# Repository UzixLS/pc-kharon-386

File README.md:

## Kharon-386
10x10cm IBM PC compatible machine with 386 CPU, integrated VGA and sound.

More random photos: [link](https://cloud.err200.net/index.php/s/73TR85tYZkMm8Ax?path=%2Fkharon-386)

### Tech specs
* M6117D System-On-Chip with integrated 386SX40 (almost compatible) CPU and M1217B chipset
* 4MB RAM
* TVGA9000i VGA video
* ES1868F SoundBlasterPro-compatible sound
* SAM2695 MIDI synthesizer
* ESP8266 WiFi module
* PS/2 keyboard and mouse inputs
* 2xCOM ports
* CF card slot
* Real-time clock (RTC) with backup battery
* Integrated PC-speaker
* 5.1V microUSB power
* Two 4-layer 10x10cm PCBs + front/back panel PCB
* G738 or G706 enclosure

### Navigation
[release/pcb_main.rev.A1.pdf](release/pcb_main.rev.A1.pdf) - motherboard schematic and bill of materials  
[release/pcb_top.rev.A1.pdf](release/pcb_top.rev.A1.pdf) - video&sound board schematic and bill of materials  
[release/bom_interactive_main.rev.A1.html](https://htmlpreview.github.io/?https://github.com/UzixLS/pc-kharon-386/blob/master/release/bom_interactive_main.rev.A1.html) - motherboard interactive BOM  
[release/bom_interactive_top.rev.A1.html](https://htmlpreview.github.io/?https://github.com/UzixLS/pc-kharon-386/blob/master/release/bom_interactive_top.rev.A1.html) - video&sound board interactive BOM  
[release/gerber_main.rev.A1.zip](release/gerber_main.rev.A1.zip) - motherboard fabrication files  
[release/gerber_top.rev.A1.zip](release/gerber_top.rev.A1.zip) - video&sound board fabrication files  
[release/gerber_covers.rev.A.zip](release/gerber_covers.rev.A.zip) - front and back panel fabrication files  
[roms/M6117 - award+ami.bin](roms/M6117%20-%20award+ami.bin) - main BIOS image  
[roms/tvga9000i - D3.51 + D4.01E.bin](roms/tvga9000i%20-%20D3.51%20%2B%20D4.01E.bin) - VGA BIOS image  
[software/msdos622_compactflash_2GB.7z](software/msdos622_compactflash_2GB.7z) - CF card image with preinstalled MS-DOS 6.22 and all necessary drivers

### WiFi module
There is two options how to use WiFi module:
1. Zimodem ([link](https://github.com/bozimmerman/Zimodem)) - provides ability to connect to BBS via any terminal without using additional software. WiFi module is connected to COM4, so you can use any terminal to communicate with it using AT commands.
2. esp_slip_router ([link](https://github.com/martin-ger/esp_slip_router)) - provides ability to connect your machine to IP network just like as Ethernet. You need ETHERSLIP or similar packet driver for DOS.

To upload firmware you need USB-UART adapter with 3.3V signal levels. Connect GND, RX and TX lines to esp header located on main PCB at left, install BOOT/GND jumper and follow any ESP8266 firmware update guide that is available on the internet.

### Sound mixer
MIDI synthesizer is connected to the AUXB sound input of ES1868F. Usually this input named as "CD input" in mixer software.  
PC speaker is connected to the AUXA input.  
To obtain a minimum noise level, it is recommended to disable line input in the mixer.

### Changelog & current status
Main PCB:
* Rev.A - first release. Please note the [errata](pcb_main/rev.A/ERRATA.txt);
* Rev.A1 - fixed all rev.A issues; added switch for BIOS variant select; added optional -5V source. Please note the [errata](pcb_main/rev.A1/ERRATA.txt).

Top PCB:
* Rev.A - first release. Please note the [errata](pcb_top/rev.A/ERRATA.txt);
* Rev.A1 - fixed all rev.A issues; added switch for VGA BIOS variant select; removed VGA-disable switch; added EEPROM for ES1868.

Covers PCB:
* Rev.A - first release.

### Related projects
I want to express my appreciation to the authors of the following projects, which served as inspiration and as reference for my development:

[http://www.alexandrugroza.ro/microelectronics/system-design/isa-80386dx-sbmc/index.html](http://www.alexandrugroza.ro/microelectronics/system-design/isa-80386dx-sbmc/index.html) - 80386DX ISA single board microcomputer by Alexandru Groza  
[https://bitbucket.org/Haper/poisk-2-mainboard/src/master/](https://bitbucket.org/Haper/poisk-2-mainboard/src/master/) - XT compatible 8086-based machine, reverse engineered by Andrew Khapoknysh ([details](https://habr.com/ru/articles/407265/))  
[http://www.malinov.com/Home/sergeys-projects/xi-8088](http://www.malinov.com/Home/sergeys-projects/xi-8088) - IBM PC/XT compatible processor board in ISA board form factor by by Sergey Kiselev  
[https://github.com/skiselev/micro_8088](https://github.com/skiselev/micro_8088) - IBM XT compatible processor board based on Faraday FE2010 chipset by Sergey Kiselev  
[https://github.com/monotech/NuXT](https://github.com/monotech/NuXT) -  MicroATX Turbo XT Motherboard, with VGA, floppy, CF, serial by Monotech  
[http://www.malinov.com/Home/sergeys-projects/isa-supervga](http://www.malinov.com/Home/sergeys-projects/isa-supervga) - ISA Super VGA card based on the Trident TVGA9000i Super VGA controller IC by Sergey Kiselev  
[https://github.com/monotech/PC104-SVGA](https://github.com/monotech/PC104-SVGA) - 8088-compatible 8-bit ISA PC/104 SVGA card by Monotech
[https://github.com/hkzlab/ES1868_ISA8](https://github.com/hkzlab/ES1868_ISA8) - ISA 8bit sound card based on the ES1868F sound chip by hkzlab

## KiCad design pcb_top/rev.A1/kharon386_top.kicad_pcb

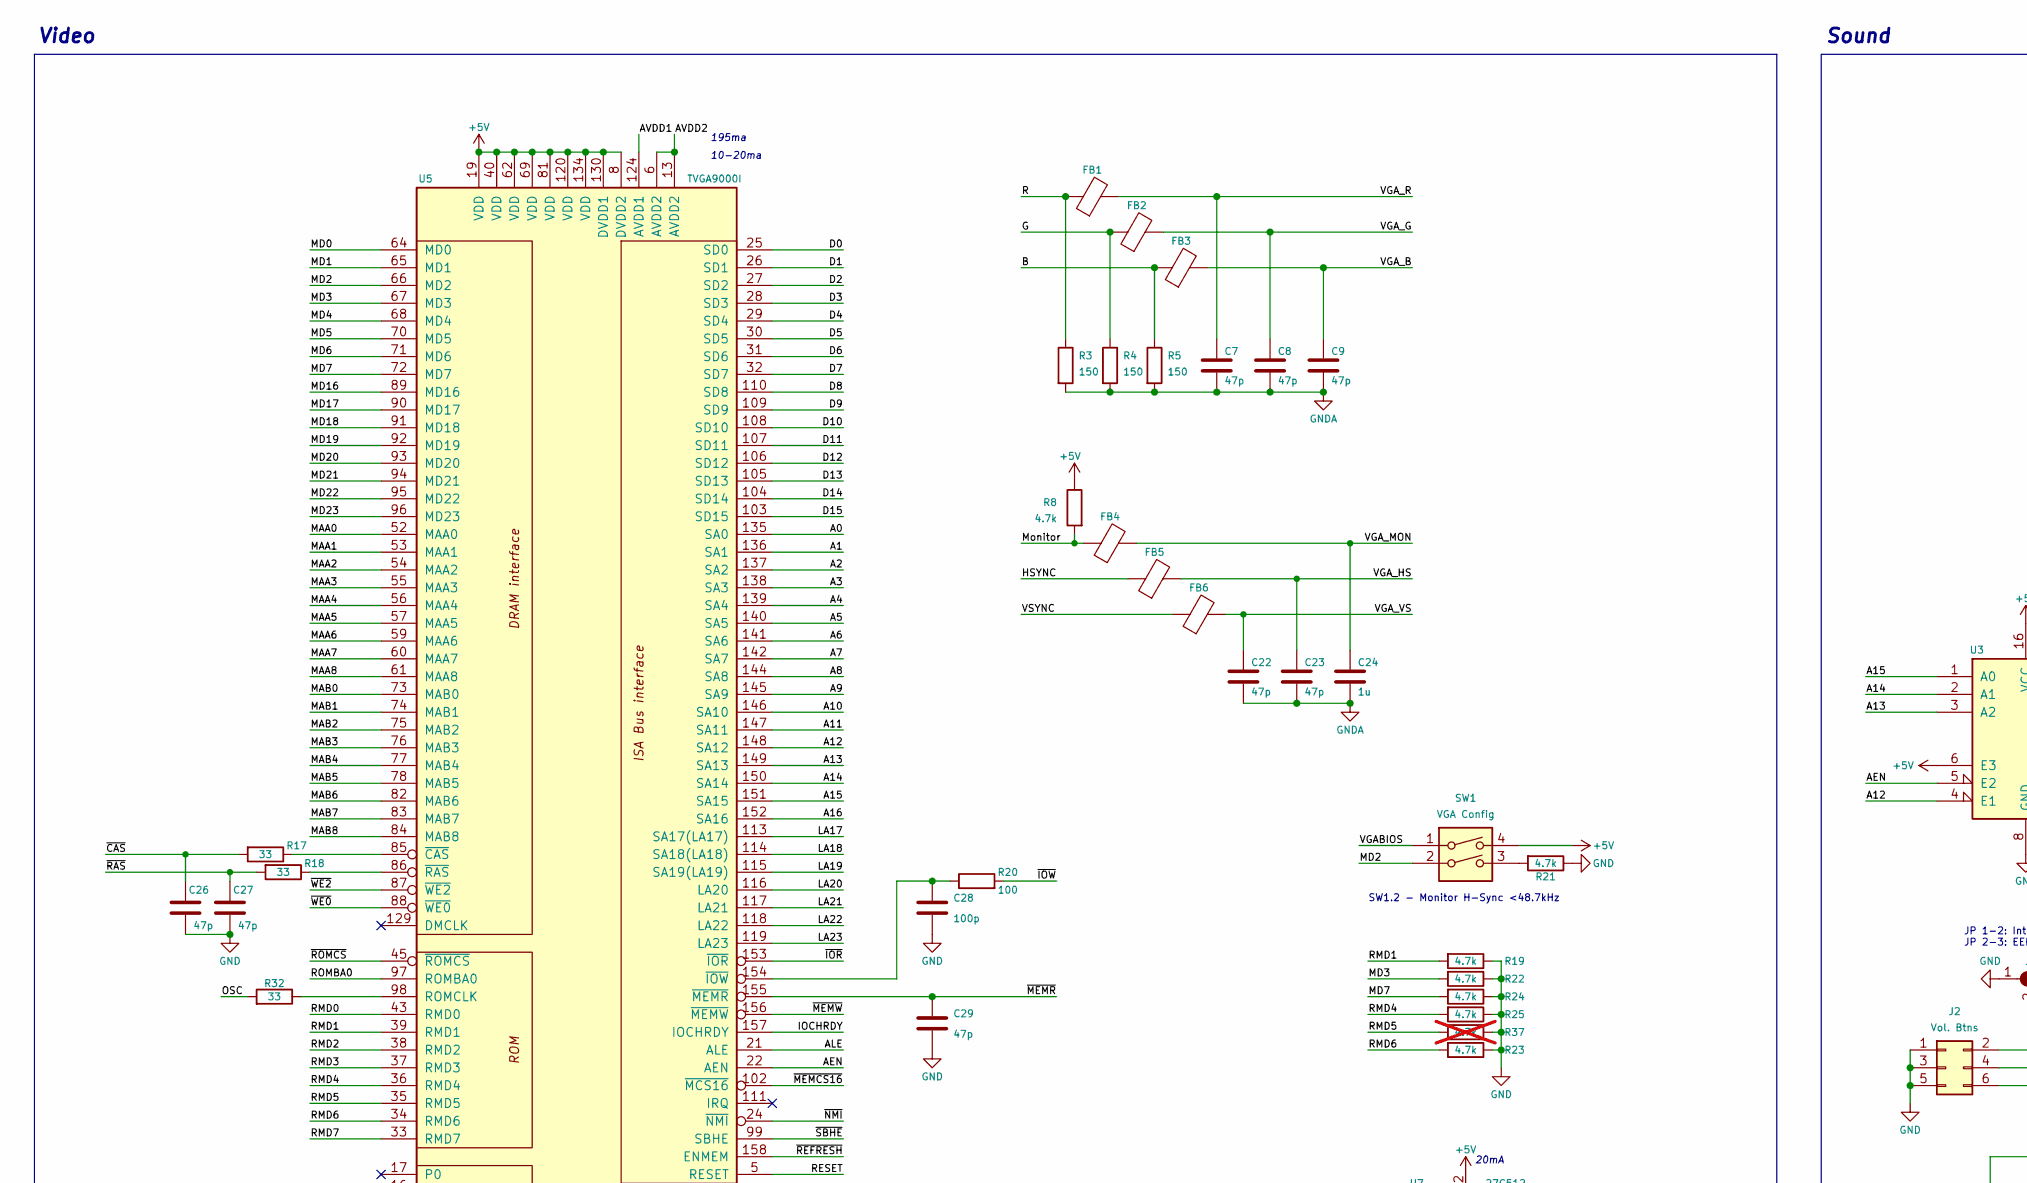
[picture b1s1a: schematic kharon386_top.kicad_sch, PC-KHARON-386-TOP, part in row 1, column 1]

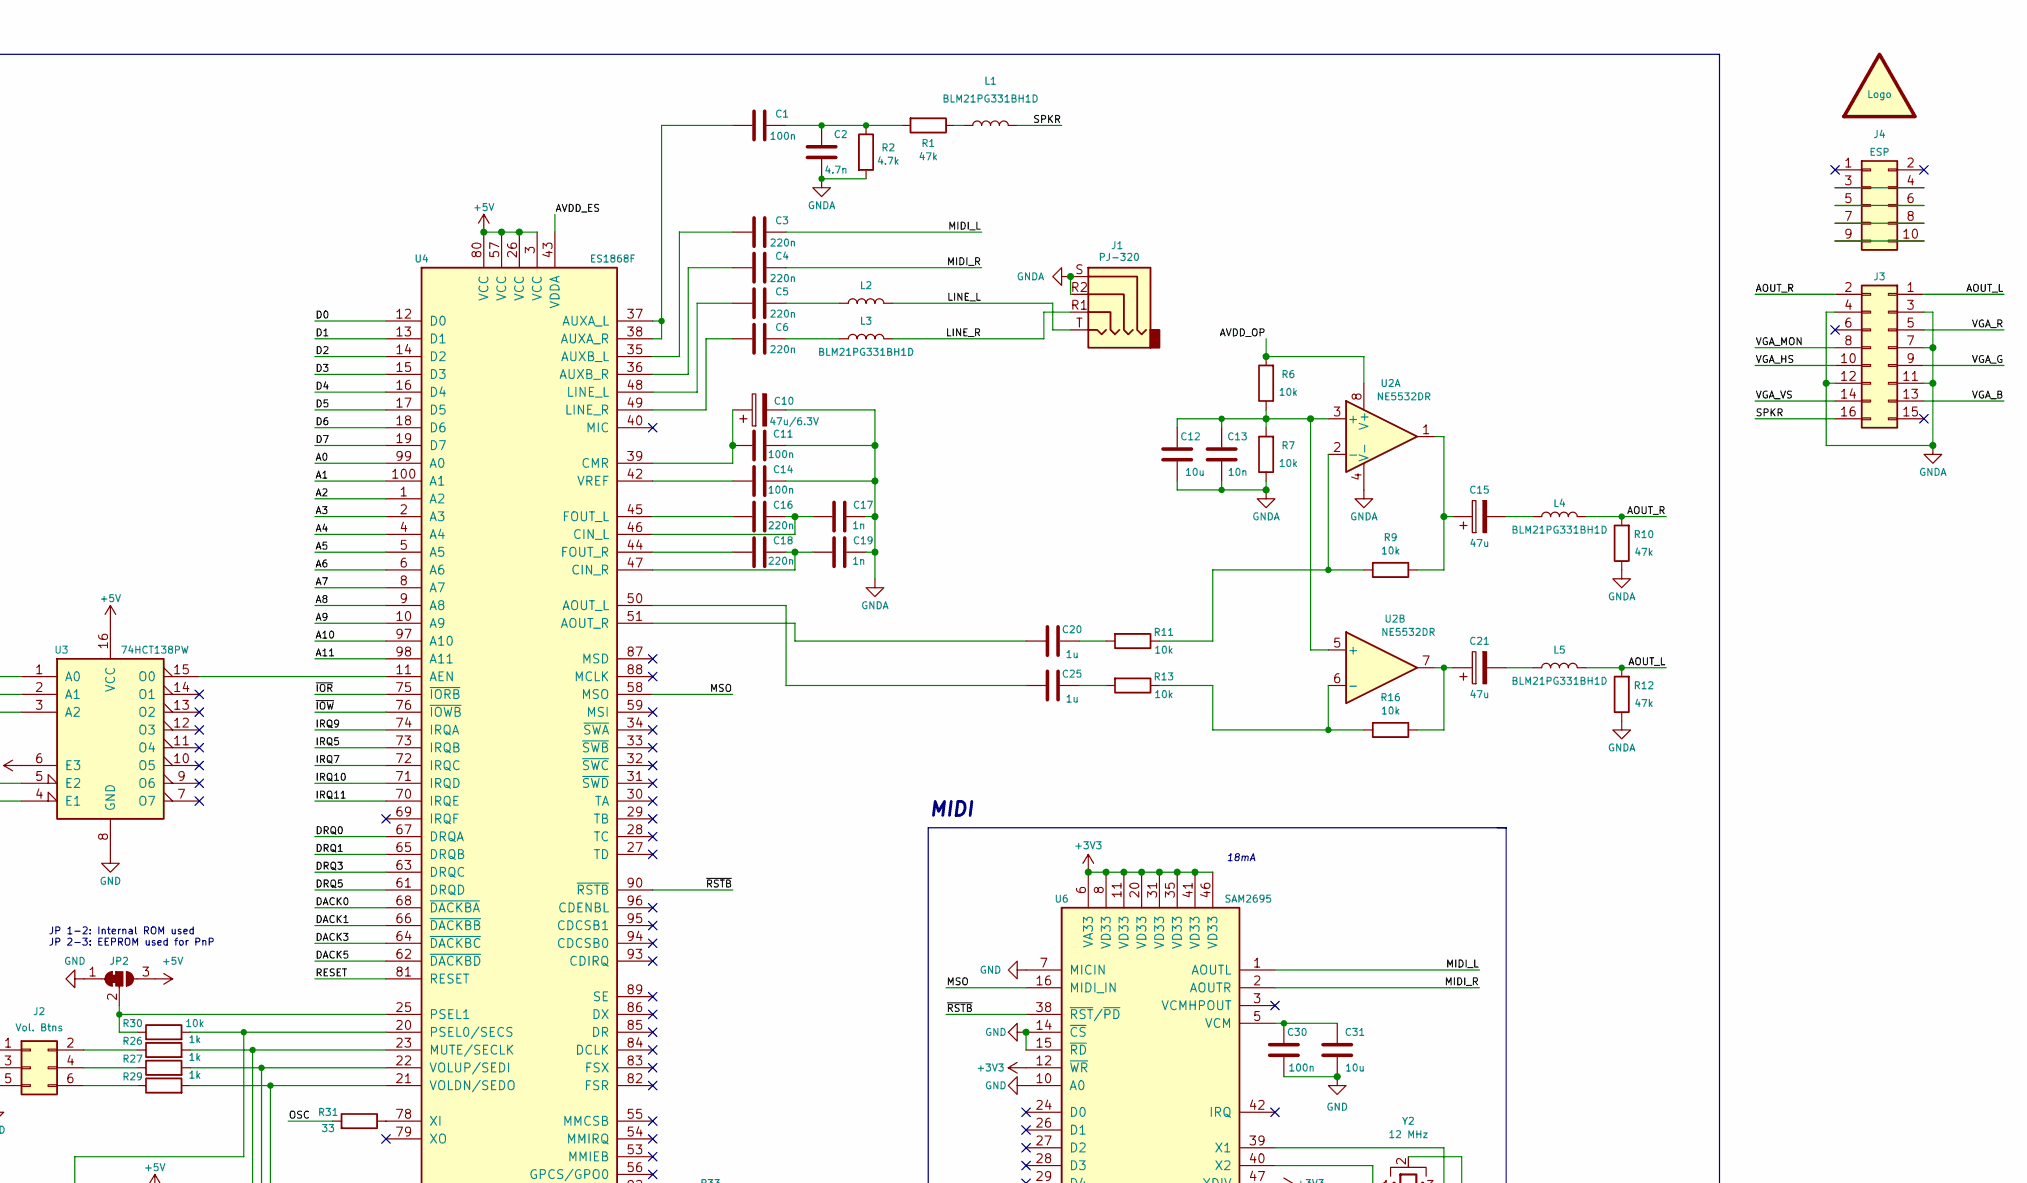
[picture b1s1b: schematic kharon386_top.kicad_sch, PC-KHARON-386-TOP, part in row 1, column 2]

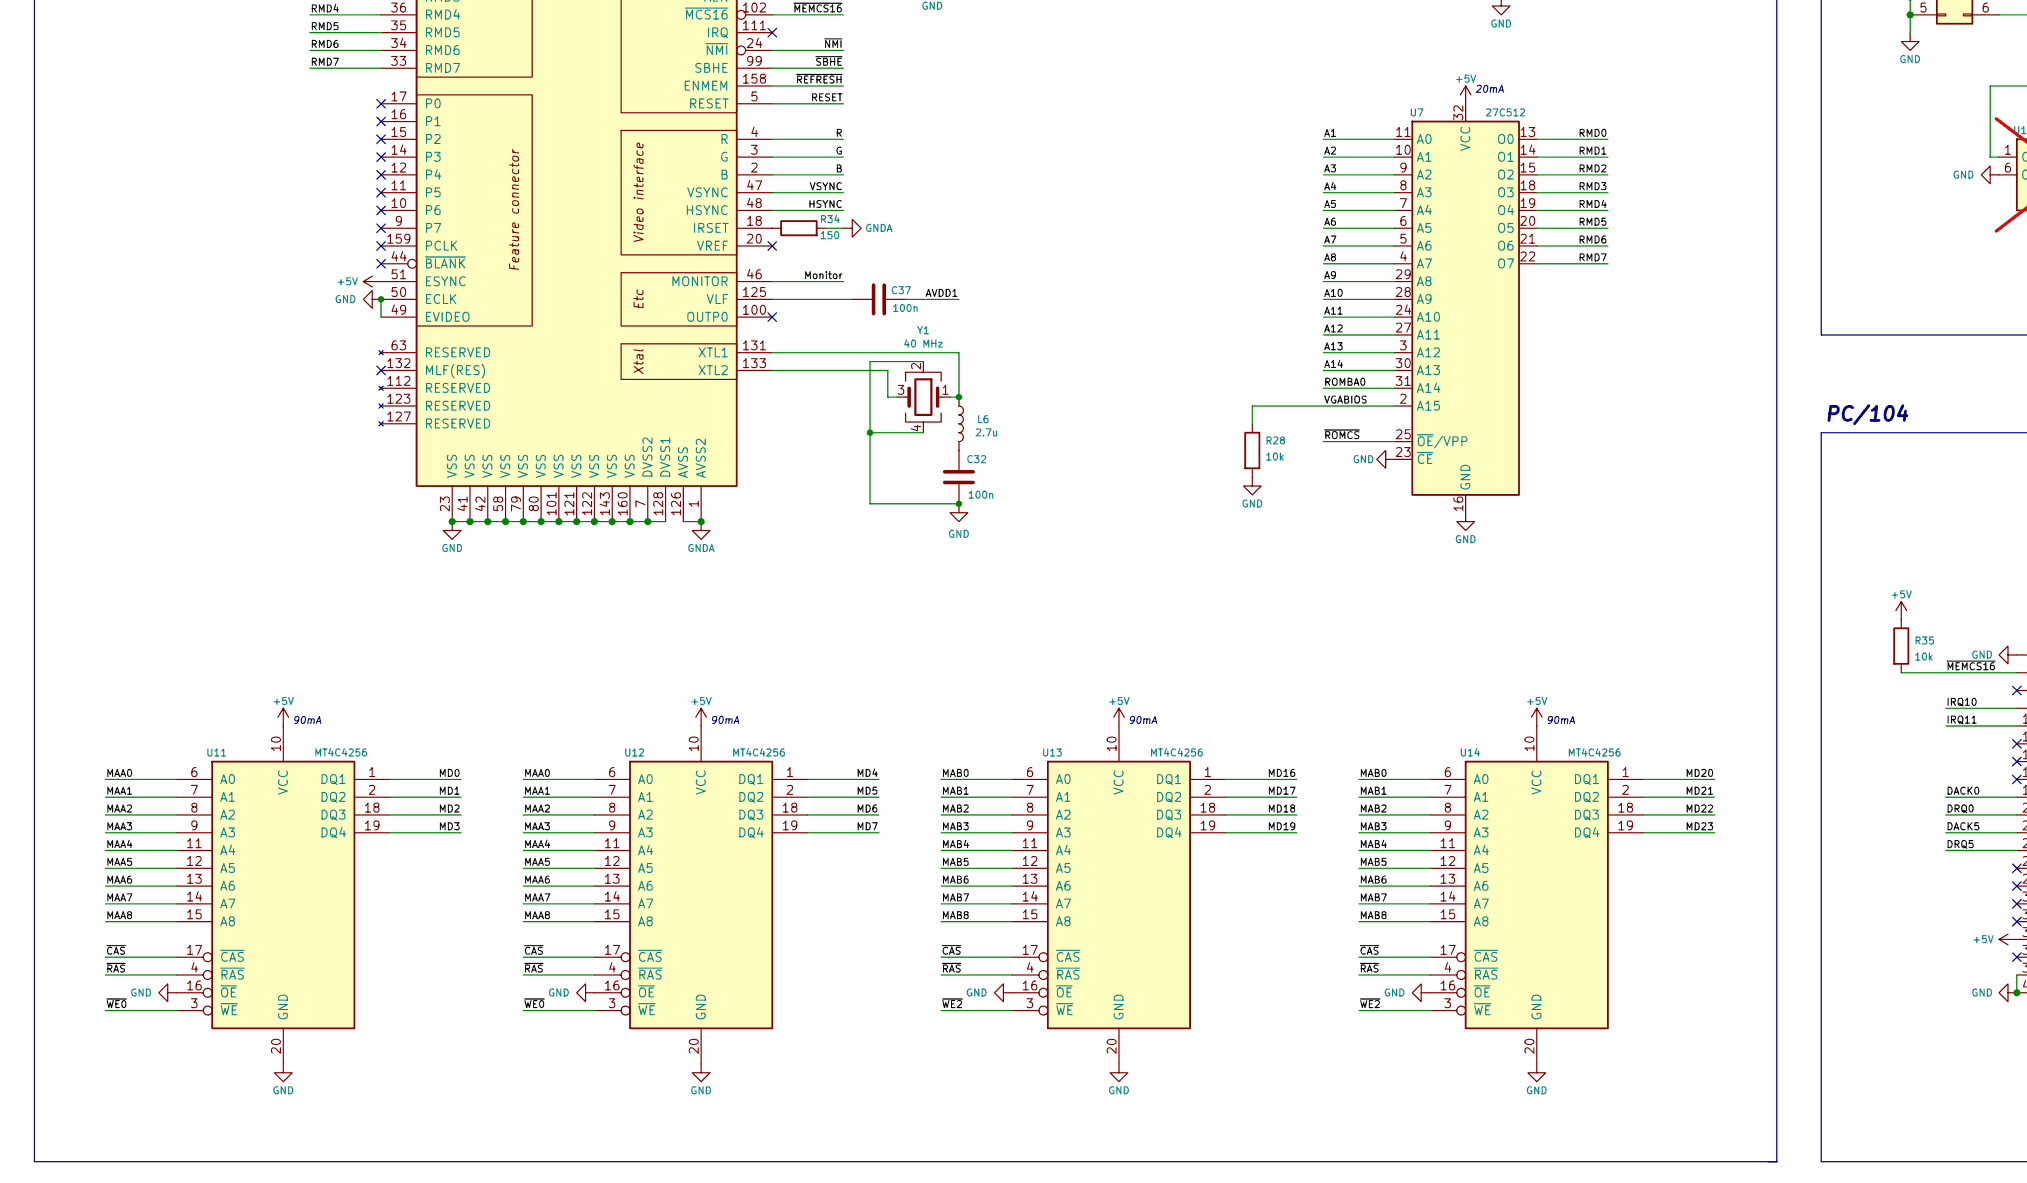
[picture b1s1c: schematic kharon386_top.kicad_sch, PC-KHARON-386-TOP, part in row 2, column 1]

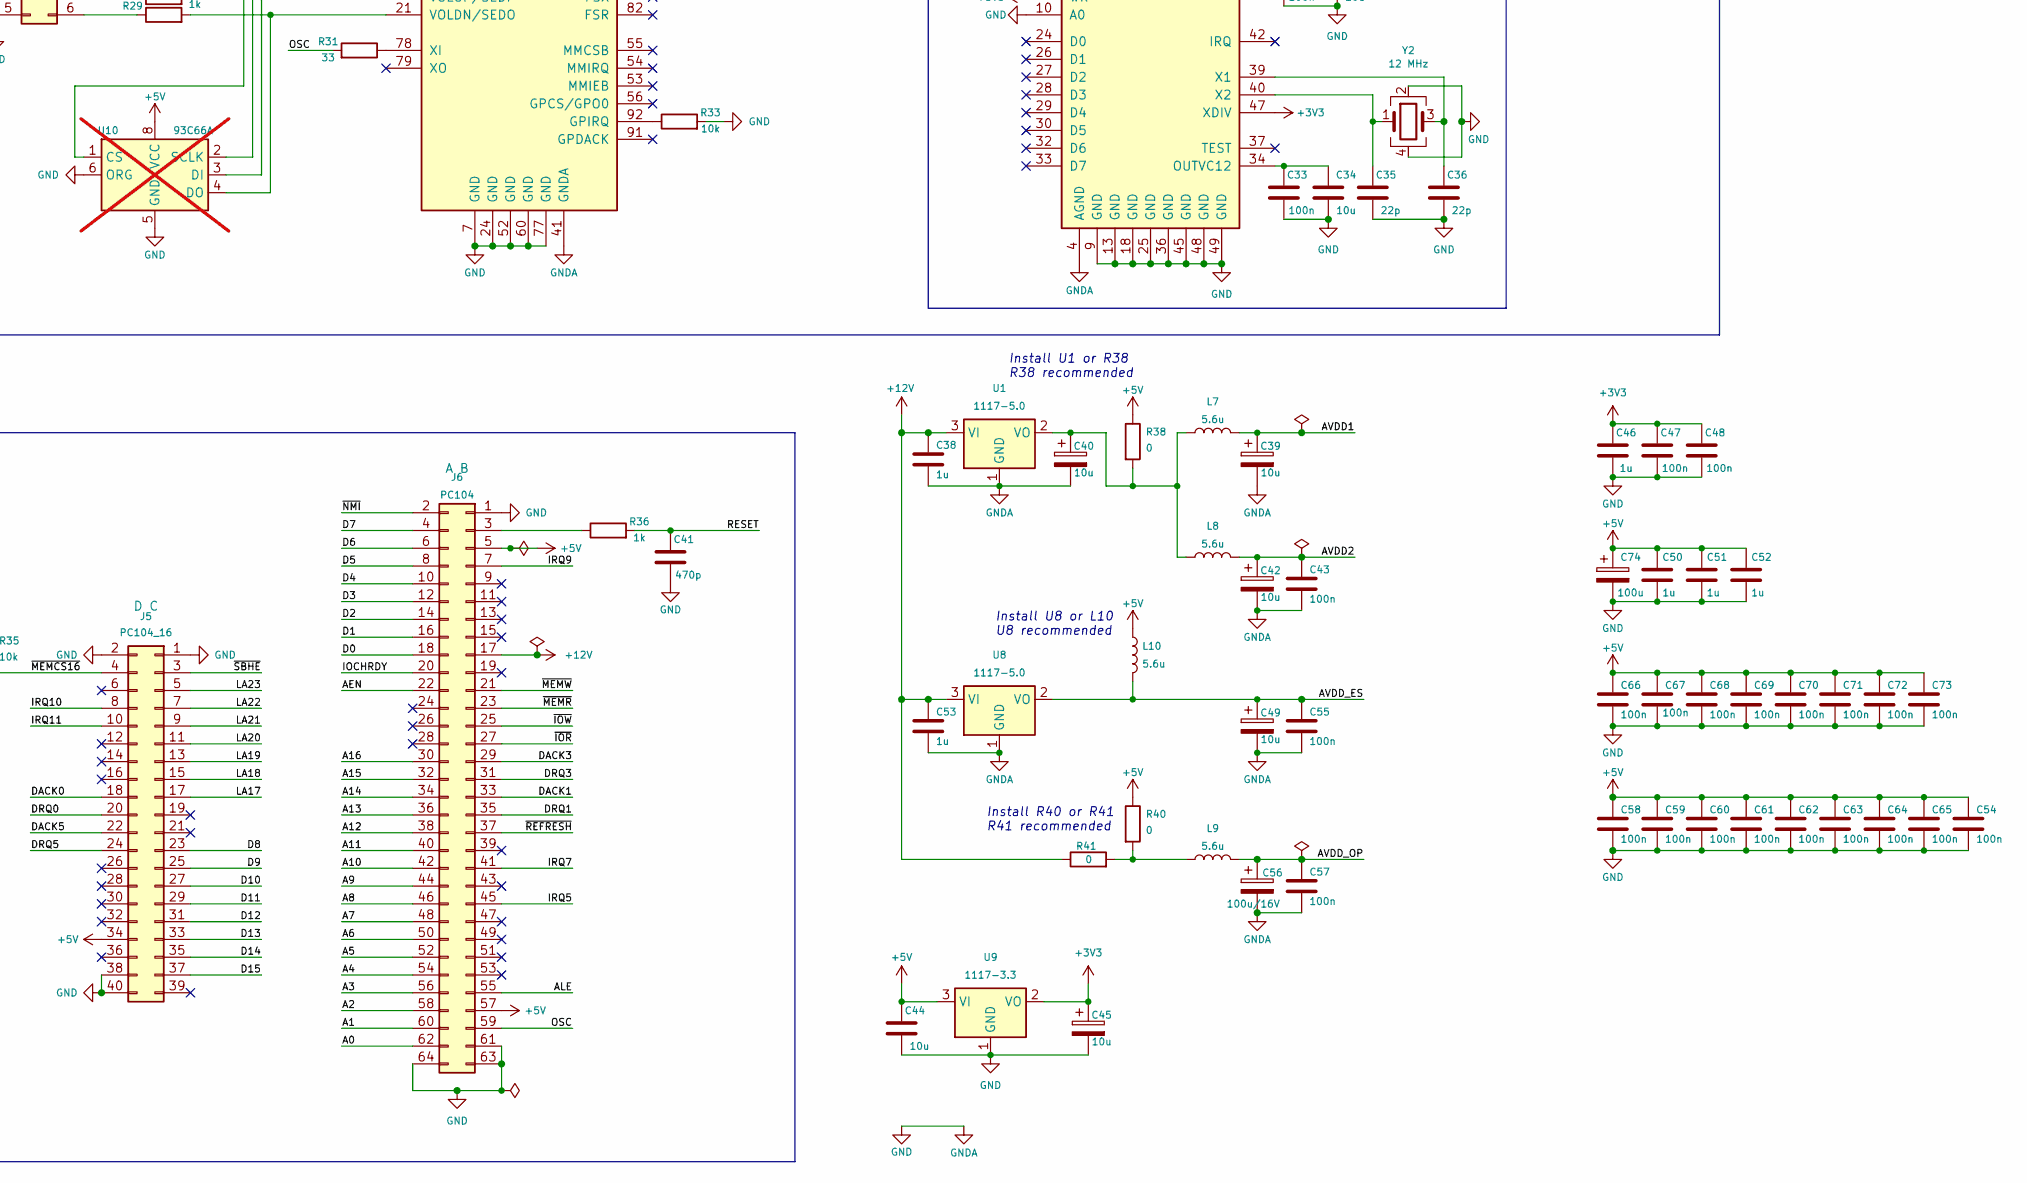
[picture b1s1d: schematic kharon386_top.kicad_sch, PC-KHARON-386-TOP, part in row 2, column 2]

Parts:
C1, C11, C14, C30, C32, C33, C37, C43, C47, C48, C54, C55, C57, C58, C59, C60, C61, C62, C63, C64, C65, C66, C67, C68, C69, C70, C71, C72, C73: 100n; C_0603_1608Metric_Pad1.08x0.95mm_HandSolder
C2: 4.7n; C_0603_1608Metric_Pad1.08x0.95mm_HandSolder
C3, C4, C5, C6, C16, C18: 220n; C_0603_1608Metric_Pad1.08x0.95mm_HandSolder
C7, C8, C9, C22, C23, C26, C27, C29: 47p; C_0603_1608Metric_Pad1.08x0.95mm_HandSolder
C10: 47u/6.3V; CP_EIA-3528-21_Kemet-B_Pad1.50x2.35mm_HandSolder
C12, C31, C34, C44: 10u; C_0805_2012Metric_Pad1.18x1.45mm_HandSolder
C13: 10n; C_0603_1608Metric_Pad1.08x0.95mm_HandSolder
C15, C21: 47u; CP_EIA-3528-21_Kemet-B_Pad1.50x2.35mm_HandSolder
C17, C19: 1n; C_0603_1608Metric_Pad1.08x0.95mm_HandSolder
C20, C24, C25, C38, C46, C50, C51, C52, C53: 1u; C_0603_1608Metric_Pad1.08x0.95mm_HandSolder
C28: 100p; C_0603_1608Metric_Pad1.08x0.95mm_HandSolder
C35, C36: 22p; C_0603_1608Metric_Pad1.08x0.95mm_HandSolder
C39, C40, C42, C45, C49: 10u; CP_EIA-3216-18_Kemet-A_Pad1.58x1.35mm_HandSolder
C41: 470p; C_0603_1608Metric_Pad1.08x0.95mm_HandSolder
C56: 100u/16V; CP_EIA-6032-28_Kemet-C_Pad2.25x2.35mm_HandSolder
C74: 100u; CP_EIA-7343-31_Kemet-D_Pad2.25x2.55mm_HandSolder
FB1, FB2, FB3, FB4, FB5, FB6: Ferrite_Bead; L_0805_2012Metric_Pad1.15x1.40mm_HandSolder
J1: PJ-320; PJ-320A_D
J2: Vol. Btns; PinHeader_2x03_P2.54mm_Vertical
J3: Conn_02x07_Odd_Even; PinHeader_2x08_P2.54mm_Vertical
J4: ESP; PinSocket_2x05_P2.54mm_Vertical
J5: PC104_16; PinHeader_2x20_P2.54mm_Vertical
J6: PC104; PinHeader_2x32_P2.54mm_Vertical
JP2: SolderJumper_3_Bridged12; SolderJumper-3_P1.3mm_Bridged12_RoundedPad1.0x1.5mm_NumberL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
L1, L2, L3, L4, L5: BLM21PG331BH1D; L_0805_2012Metric_Pad1.15x1.40mm_HandSolder
L6: 2.7u; L_0805_2012Metric_Pad1.15x1.40mm_HandSolder
L7, L8, L9, L10: 5.6u; L_1210_3225Metric_Pad1.42x2.65mm_HandSolder
LOGO1: graphic; black-mage-12.5x8.6
R1, R10, R12: 47k; R_0603_1608Metric_Pad0.98x0.95mm_HandSolder
R2, R8, R19, R21, R22, R23, R24, R25: 4.7k; R_0603_1608Metric_Pad0.98x0.95mm_HandSolder
R3, R4, R5, R34: 150; R_0603_1608Metric_Pad0.98x0.95mm_HandSolder
R6, R7, R9, R11, R13, R16, R28, R30, R33, R35: 10k; R_0603_1608Metric_Pad0.98x0.95mm_HandSolder
R17, R18, R31, R32: 33; R_0603_1608Metric_Pad0.98x0.95mm_HandSolder
R20: 100; R_0603_1608Metric_Pad0.98x0.95mm_HandSolder
R26, R27, R29, R36: 1k; R_0603_1608Metric_Pad0.98x0.95mm_HandSolder
R37: 4.7k; R_0603_1608Metric_Pad0.98x0.95mm_HandSolder; not fitted
R38, R40, R41: 0; R_0805_2012Metric_Pad1.20x1.40mm_HandSolder
SW1: VGA Config; SW_DIP_SPSTx02_Slide_6.7x6.64mm_W7.62mm_P2.54mm_LowProfile
U1, U8: 1117-5.0; SOT-223-3_TabPin2
U2: NE5532DR; SOIC-8_3.9x4.9mm_P1.27mm
U3: 74HCT138PW; TSSOP-16_4.4x5mm_P0.65mm
U4: ES1868F; PQFP-100_14x20mm_P0.65mm_ESxxx
U5: TVGA9000I; PQFP-160_28x28mm_P0.65mm_LongPads
U6: SAM2695; QFN-48-1EP_6x6mm_P0.4mm_EP4.2x4.2mm
U7: 27C512; PLCC-32_11.4x14.0mm_P1.27mm-longpads
U9: 1117-3.3; SOT-223-3_TabPin2
U10: 93C66A; SOIC-8_3.9x4.9mm_P1.27mm; not fitted
U11, U12, U13, U14: MT4C4256; DIP-20_W7.62mm
Y1: 40 MHz; Crystal_SMD_SeikoEpson_TSX3225-4Pin_3.2x2.5mm_HandSoldering
Y2: 12 MHz; Crystal_SMD_SeikoEpson_TSX3225-4Pin_3.2x2.5mm_HandSoldering

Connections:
+3V3: C45.1, C46.2, C47.2, C48.2, U6.6 (VA33), U6.8 (VD33), U6.11 (VD33), U6.12 (~WR), U6.20 (VD33), U6.31 (VD33), U6.35 (VD33), U6.41 (VD33), U6.46 (VD33), U6.47 (XDIV), U9.2 (VO)
+5V: C44.2, C50.1, C51.1, C52.1, C54.1, C58.1, C59.1, C60.1, C61.1, C62.1, C63.1, C64.1, C65.1, C66.1, C67.1, C68.1, C69.1, C70.1, C71.1, C72.1, C73.1, C74.1, J5.34, J6.5, J6.57, JP2.3 (B), L10.1, R8.1, R35.1, R38.1, R40.1, SW1.4, U3.6 (E3), U3.16 (VCC), U4.3 (VCC), U4.26 (VCC), U4.57 (VCC), U4.80 (VCC), U5.8 (DVDD2), U5.19 (VDD), U5.40 (VDD), U5.51 (ESYNC), U5.62 (VDD), U5.69 (VDD), U5.81 (VDD), U5.120 (VDD), U5.130 (DVDD1), U5.134 (VDD), U7.32 (VCC), U9.3 (VI), U10.8 (VCC), U11.10 (VCC), U12.10 (VCC), U13.10 (VCC), U14.10 (VCC)
+12V: C38.1, C53.1, J6.17, R41.1, U1.3 (VI), U8.3 (VI)
/A0: J6.62, U4.99 (A0), U5.135 (SA0)
/A1: J6.60, U4.100 (A1), U5.136 (SA1), U7.11 (A0)
/A2: J6.58, U4.1 (A2), U5.137 (SA2), U7.10 (A1)
/A3: J6.56, U4.2 (A3), U5.138 (SA3), U7.9 (A2)
/A4: J6.54, U4.4 (A4), U5.139 (SA4), U7.8 (A3)
/A5: J6.52, U4.5 (A5), U5.140 (SA5), U7.7 (A4)
/A6: J6.50, U4.6 (A6), U5.141 (SA6), U7.6 (A5)
/A7: J6.48, U4.8 (A7), U5.142 (SA7), U7.5 (A6)
/A8: J6.46, U4.9 (A8), U5.144 (SA8), U7.4 (A7)
/A9: J6.44, U4.10 (A9), U5.145 (SA9), U7.29 (A8)
/A10: J6.42, U4.97 (A10), U5.146 (SA10), U7.28 (A9)
/A11: J6.40, U4.98 (A11), U5.147 (SA11), U7.24 (A10)
/A12: J6.38, U3.4 (E1), U5.148 (SA12), U7.27 (A11)
/A13: J6.36, U3.3 (A2), U5.149 (SA13), U7.3 (A12)
/A14: J6.34, U3.2 (A1), U5.150 (SA14), U7.30 (A13)
/A15: J6.32, U3.1 (A0), U5.151 (SA15)
/A16: J6.30, U5.152 (SA16)
/AEN: J6.22, U3.5 (E2), U5.22 (AEN)
/ALE: J6.55, U5.21 (ALE)
/AOUT_L: J3.1, L5.2, R12.2
/AOUT_R: J3.2, L4.2, R10.2
/AVDD1: C37.2, C39.1, L7.2, U5.124 (AVDD1)
/AVDD2: C42.1, C43.1, L8.2, U5.6 (AVDD2), U5.13 (AVDD2)
/AVDD_ES: C49.1, C55.1, L10.2, U4.43 (VDDA), U8.2 (VO)
/AVDD_OP: C56.1, C57.1, L9.2, R6.2, U2.8 (V+)
/B: FB3.1, R5.1, U5.2 (B)
/D0: J6.18, U4.12 (D0), U5.25 (SD0)
/D1: J6.16, U4.13 (D1), U5.26 (SD1)
/D2: J6.14, U4.14 (D2), U5.27 (SD2)
/D3: J6.12, U4.15 (D3), U5.28 (SD3)
/D4: J6.10, U4.16 (D4), U5.29 (SD4)
/D5: J6.8, U4.17 (D5), U5.30 (SD5)
/D6: J6.6, U4.18 (D6), U5.31 (SD6)
/D7: J6.4, U4.19 (D7), U5.32 (SD7)
/D8: J5.23, U5.110 (SD8)
/D9: J5.25, U5.109 (SD9)
/D10: J5.27, U5.108 (SD10)
/D11: J5.29, U5.107 (SD11)
/D12: J5.31, U5.106 (SD12)
/D13: J5.33, U5.105 (SD13)
/D14: J5.35, U5.104 (SD14)
/D15: J5.37, U5.103 (SD15)
/DACK0: J5.18, U4.68 (~DACKBA)
/DACK1: J6.33, U4.66 (~DACKBB)
/DACK3: J6.29, U4.64 (~DACKBC)
/DACK5: J5.22, U4.62 (~DACKBD)
/DRQ0: J5.20, U4.67 (DRQA)
/DRQ1: J6.35, U4.65 (DRQB)
/DRQ3: J6.31, U4.63 (DRQC)
/DRQ5: J5.24, U4.61 (DRQD)
/G: FB2.1, R4.1, U5.3 (G)
/HSYNC: FB5.1, U5.48 (HSYNC)
/IOCHRDY: J6.20, U5.157 (IOCHRDY)
/IRQ5: J6.45, U4.73 (IRQB)
/IRQ7: J6.41, U4.72 (IRQC)
/IRQ9: J6.7, U4.74 (IRQA)
/IRQ10: J5.8, U4.71 (IRQD)
/IRQ11: J5.10, U4.70 (IRQE)
/LA17: J5.17, U5.113 (SA17(LA17))
/LA18: J5.15, U5.114 (SA18(LA18))
/LA19: J5.13, U5.115 (SA19(LA19))
/LA20: J5.11, U5.116 (LA20)
/LA21: J5.9, U5.117 (LA21)
/LA22: J5.7, U5.118 (LA22)
/LA23: J5.5, U5.119 (LA23)
/LINE_L: J1.T, L2.2
/LINE_R: J1.R1, L3.2
/MAA0: U5.52 (MAA0), U11.6 (A0), U12.6 (A0)
/MAA1: U5.53 (MAA1), U11.7 (A1), U12.7 (A1)
/MAA2: U5.54 (MAA2), U11.8 (A2), U12.8 (A2)
/MAA3: U5.55 (MAA3), U11.9 (A3), U12.9 (A3)
/MAA4: U5.56 (MAA4), U11.11 (A4), U12.11 (A4)
/MAA5: U5.57 (MAA5), U11.12 (A5), U12.12 (A5)
/MAA6: U5.59 (MAA6), U11.13 (A6), U12.13 (A6)
/MAA7: U5.60 (MAA7), U11.14 (A7), U12.14 (A7)
/MAA8: U5.61 (MAA8), U11.15 (A8), U12.15 (A8)
/MAB0: U5.73 (MAB0), U13.6 (A0), U14.6 (A0)
/MAB1: U5.74 (MAB1), U13.7 (A1), U14.7 (A1)
/MAB2: U5.75 (MAB2), U13.8 (A2), U14.8 (A2)
/MAB3: U5.76 (MAB3), U13.9 (A3), U14.9 (A3)
/MAB4: U5.77 (MAB4), U13.11 (A4), U14.11 (A4)
/MAB5: U5.78 (MAB5), U13.12 (A5), U14.12 (A5)
/MAB6: U5.82 (MAB6), U13.13 (A6), U14.13 (A6)
/MAB7: U5.83 (MAB7), U13.14 (A7), U14.14 (A7)
/MAB8: U5.84 (MAB8), U13.15 (A8), U14.15 (A8)
/MD0: U5.64 (MD0), U11.1 (DQ1)
/MD1: U5.65 (MD1), U11.2 (DQ2)
/MD2: SW1.2, U5.66 (MD2), U11.18 (DQ3)
/MD3: R22.2, U5.67 (MD3), U11.19 (DQ4)
/MD4: U5.68 (MD4), U12.1 (DQ1)
/MD5: U5.70 (MD5), U12.2 (DQ2)
/MD6: U5.71 (MD6), U12.18 (DQ3)
/MD7: R24.2, U5.72 (MD7), U12.19 (DQ4)
/MD16: U5.89 (MD16), U13.1 (DQ1)
/MD17: U5.90 (MD17), U13.2 (DQ2)
/MD18: U5.91 (MD18), U13.18 (DQ3)
/MD19: U5.92 (MD19), U13.19 (DQ4)
/MD20: U5.93 (MD20), U14.1 (DQ1)
/MD21: U5.94 (MD21), U14.2 (DQ2)
/MD22: U5.95 (MD22), U14.18 (DQ3)
/MD23: U5.96 (MD23), U14.19 (DQ4)
/MIDI_L: C3.2, U6.1 (AOUTL)
/MIDI_R: C4.2, U6.2 (AOUTR)
/MSO: U4.58 (MSO), U6.16 (MIDI_IN)
/Monitor: FB4.1, R8.2, U5.46 (MONITOR)
/OSC: J6.59, R31.2, R32.2
/R: FB1.1, R3.1, U5.4 (R)
/RESET: C41.1, R36.2, U4.81 (RESET), U5.5 (RESET)
/RMD0: U5.43 (RMD0), U7.13 (O0)
/RMD1: R19.2, U5.39 (RMD1), U7.14 (O1)
/RMD2: U5.38 (RMD2), U7.15 (O2)
/RMD3: U5.37 (RMD3), U7.18 (O3)
/RMD4: R25.2, U5.36 (RMD4), U7.19 (O4)
/RMD5: R37.2, U5.35 (RMD5), U7.20 (O5)
/RMD6: R23.2, U5.34 (RMD6), U7.21 (O6)
/RMD7: U5.33 (RMD7), U7.22 (O7)
/ROMBA0: U5.97 (ROMBA0), U7.31 (A14)
/SPKR: J3.16, L1.2
/VGABIOS: R28.1, SW1.1, U7.2 (A15)
/VGA_B: C9.1, FB3.2, J3.13
/VGA_G: C8.1, FB2.2, J3.9
/VGA_HS: C23.1, FB5.2, J3.10
/VGA_MON: C24.1, FB4.2, J3.8
/VGA_R: C7.1, FB1.2, J3.5
/VGA_VS: C22.1, FB6.2, J3.14
/VSYNC: FB6.1, U5.47 (VSYNC)
/~CAS: C26.2, R17.2, U11.17 (~CAS), U12.17 (~CAS), U13.17 (~CAS), U14.17 (~CAS)
/~IOR: J6.27, U4.75 (~IORB), U5.153 (~IOR)
/~IOW: J6.25, R20.2, U4.76 (~IOWB)
/~MEMCS16: J5.4, R35.2, U5.102 (~MCS16)
/~MEMR: C29.1, J6.23, U5.155 (~MEMR)
/~MEMW: J6.21, U5.156 (~MEMW)
/~NMI: J6.2, U5.24 (~NMI)
/~RAS: C27.2, R18.2, U11.4 (~RAS), U12.4 (~RAS), U13.4 (~RAS), U14.4 (~RAS)
/~REFRESH: J6.37, U5.158 (ENMEM)
/~ROMCS: U5.45 (~ROMCS), U7.25 (~OE/VPP)
/~RSTB: U4.90 (~RSTB), U6.38 (~RST/~PD)
/~SBHE: J5.3, U5.99 (SBHE)
/~WE0: U5.88 (~WE0), U11.3 (~WE), U12.3 (~WE)
/~WE2: U5.87 (~WE2), U13.3 (~WE), U14.3 (~WE)
GND: C2.1, C7.2, C8.2, C9.2, C10.2, C11.2, C12.1, C13.1, C14.2, C17.2, C19.2, C22.2, C23.2, C24.2, C26.1, C27.1, C28.2, C29.2, C30.1, C31.1, C32.1, C33.1, C34.1, C35.1, C36.1, C38.2, C39.2, C40.2, C41.2, C42.2, C43.2, C44.1, C45.2, C46.1, C47.1, C48.1, C49.2, C50.2, C51.2, C52.2, C53.2, C54.2, C55.2, C56.2, C57.2, C58.2, C59.2, C60.2, C61.2, C62.2, C63.2, C64.2, C65.2, C66.2, C67.2, C68.2, C69.2, C70.2, C71.2, C72.2, C73.2, C74.2, J1.R2, J1.S, J2.1, J2.3, J2.5, J3.3, J3.4, J3.7, J3.11, J3.12, J5.1, J5.2, J5.38, J5.40, J6.1, J6.61, J6.63, J6.64, JP2.1 (A), R2.2, R3.2, R4.2, R5.2, R7.1, R10.1, R12.1, R19.1, R21.1, R22.1, R23.1, R24.1, R25.1, R28.2, R33.2, R34.2, R37.1, U1.1 (GND), U2.4 (V-), U3.8 (GND), U4.7 (GND), U4.24 (GND), U4.41 (GNDA), U4.52 (GND), U4.60 (GND), U4.77 (GND), U5.1 (AVSS2), U5.7 (DVSS2), U5.23 (VSS), U5.41 (VSS), U5.42 (VSS), U5.49 (EVIDEO), U5.50 (ECLK), U5.58 (VSS), U5.79 (VSS), U5.80 (VSS), U5.101 (VSS), U5.121 (VSS), U5.122 (VSS), U5.126 (AVSS), U5.128 (DVSS1), U5.143 (VSS), U5.160 (VSS), U6.4 (AGND), U6.7 (MICIN), U6.9 (GND), U6.10 (A0), U6.13 (GND), U6.14 (~CS), U6.15 (~RD), U6.18 (GND), U6.25 (GND), U6.36 (GND), U6.45 (GND), U6.48 (GND), U6.49 (GND), U7.16 (GND), U7.23 (~CE), U8.1 (GND), U9.1 (GND), U10.5 (GND), U10.6 (ORG), U11.16 (~OE), U11.20 (GND), U12.16 (~OE), U12.20 (GND), U13.16 (~OE), U13.20 (GND), U14.16 (~OE), U14.20 (GND), Y1.2, Y1.4, Y2.2, Y2.4
unnamed: C1.2, C2.2, R1.2, R2.1
unnamed: C5.2, L2.1
unnamed: C6.2, L3.1
unnamed: C15.1, R9.1, U2.1
unnamed: C15.2, L4.1
unnamed: C20.2, R11.2
unnamed: C21.1, R16.1, U2.7
unnamed: C21.2, L5.1
unnamed: C25.2, R13.2
unnamed: C32.2, L6.1
unnamed: J2.2, R26.1
unnamed: J2.4, R27.1
unnamed: J2.6, R29.1
unnamed: J4.3, J4.4
unnamed: J4.5, J4.6
unnamed: J4.7, J4.8
unnamed: J4.9, J4.10
unnamed: J6.3, R36.1
unnamed: JP2.2 (C), R30.1, U4.25 (PSEL1)
unnamed: L1.1, R1.1
unnamed: L9.1, R40.2, R41.2
unnamed: R21.2, SW1.3
unnamed: C40.1, L7.1, L8.1, R38.2, U1.2 (VO)
unnamed: C12.2, C13.2, R6.1, R7.2, U2.3 (+), U2.5 (+)
unnamed: R9.2, R11.1, U2.2 (-)
unnamed: R13.1, R16.2, U2.6 (-)
unnamed: U3.15 (O0), U4.11 (AEN)
unnamed: C25.1, U4.50 (AOUT_L)
unnamed: C20.1, U4.51 (AOUT_R)
unnamed: C1.1, U4.37 (AUXA_L), U4.38 (AUXA_R)
unnamed: C3.1, U4.35 (AUXB_L)
unnamed: C4.1, U4.36 (AUXB_R)
unnamed: C16.2, C17.1, U4.46 (CIN_L)
unnamed: C18.2, C19.1, U4.47 (CIN_R)
unnamed: C10.1, C11.1, U4.39 (CMR)
unnamed: C16.1, U4.45 (FOUT_L)
unnamed: C18.1, U4.44 (FOUT_R)
unnamed: R33.1, U4.92 (GPIRQ)
unnamed: C5.1, U4.48 (LINE_L)
unnamed: C6.1, U4.49 (LINE_R)
unnamed: C14.1, U4.42 (VREF)
unnamed: R31.1, U4.78 (XI)
unnamed: R34.1, U5.18 (IRSET)
unnamed: R32.1, U5.98 (ROMCLK)
unnamed: C37.1, U5.125 (VLF)
unnamed: L6.2, U5.131 (XTL1), Y1.1
unnamed: U5.133 (XTL2), Y1.3
unnamed: R17.1, U5.85 (~CAS)
unnamed: C28.1, R20.1, U5.154 (~IOW)
unnamed: R18.1, U5.86 (~RAS)
unnamed: C33.2, C34.2, U6.34 (OUTVC12)
unnamed: C30.2, C31.2, U6.5 (VCM)
unnamed: C36.2, U6.39 (X1), Y2.3
unnamed: C35.2, U6.40 (X2), Y2.1
unnamed: R30.2, U4.20 (PSEL0/SECS), U10.1 (CS)
unnamed: R27.2, U4.22 (VOLUP/SEDI), U10.3 (DI)
unnamed: R29.2, U4.21 (VOLDN/SEDO), U10.4 (DO)
unnamed: R26.2, U4.23 (MUTE/SECLK), U10.2 (SCLK)

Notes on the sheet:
10-20ma
JP 1-2: Internal ROM used JP 2-3: EEPROM used for PnP
SW1.2 - Monitor H-Sync <48.7kHz
90mA
18mA
195ma
Install U1 or R38 R38 recommended
Sound
Video
Install U8 or L10 U8 recommended
MIDI
20mA
Install R40 or R41 R41 recommended
PC/104

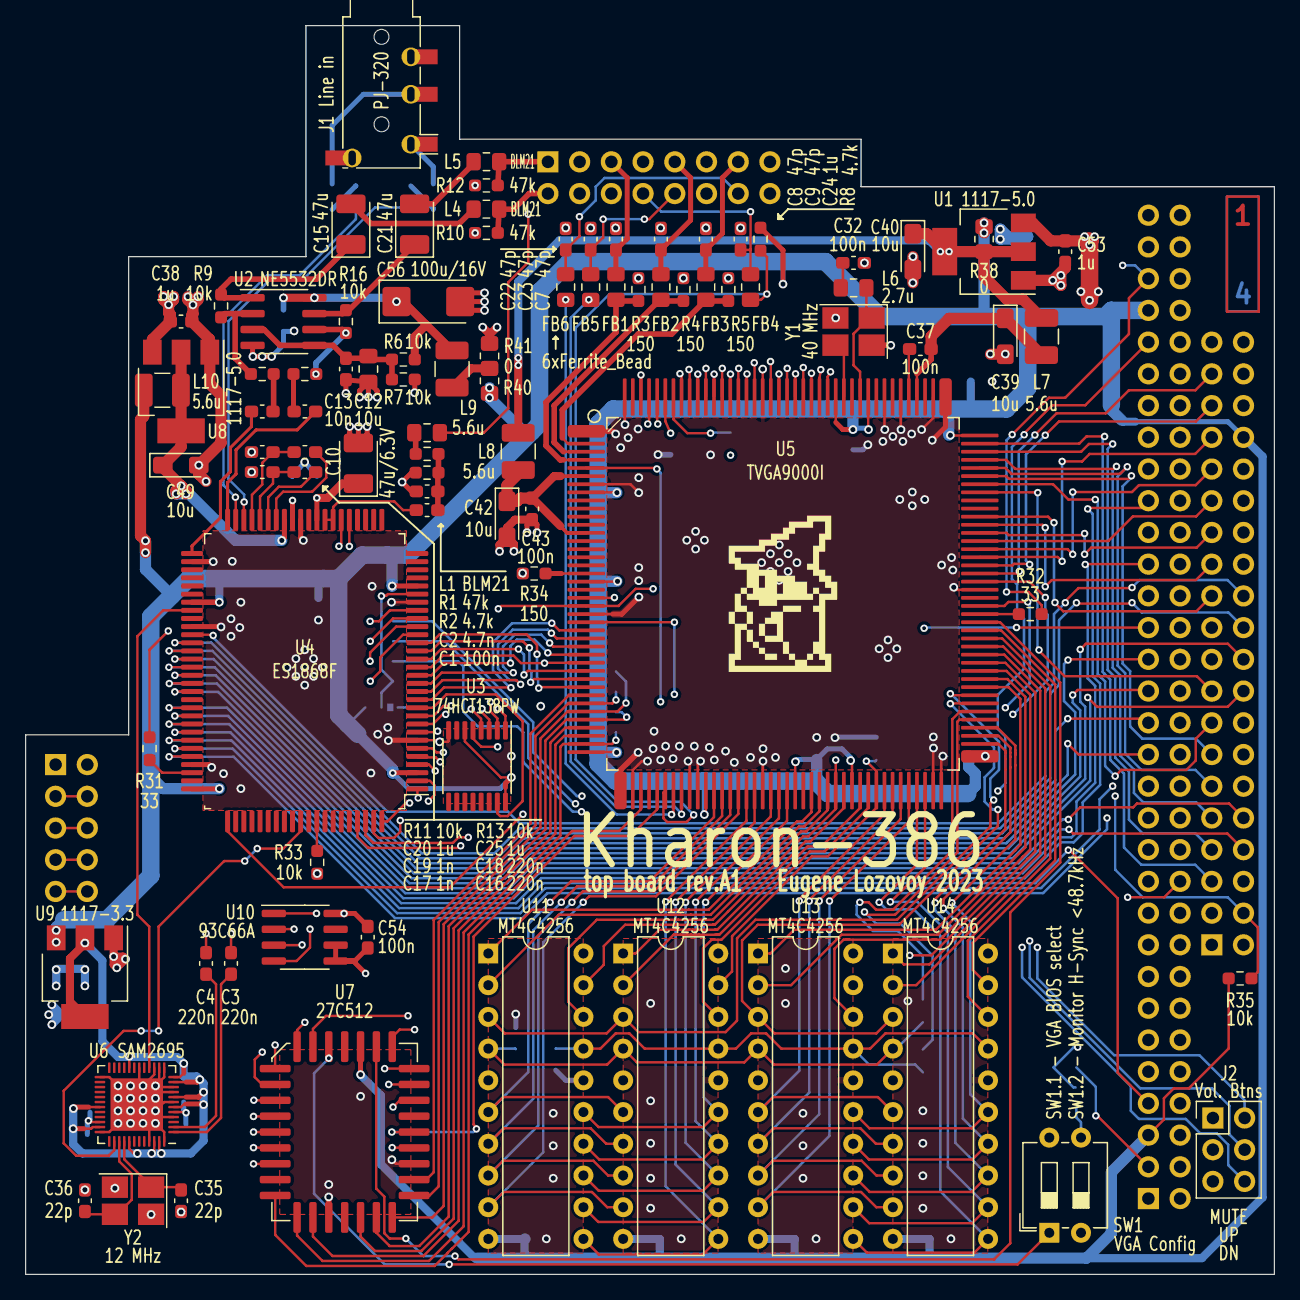
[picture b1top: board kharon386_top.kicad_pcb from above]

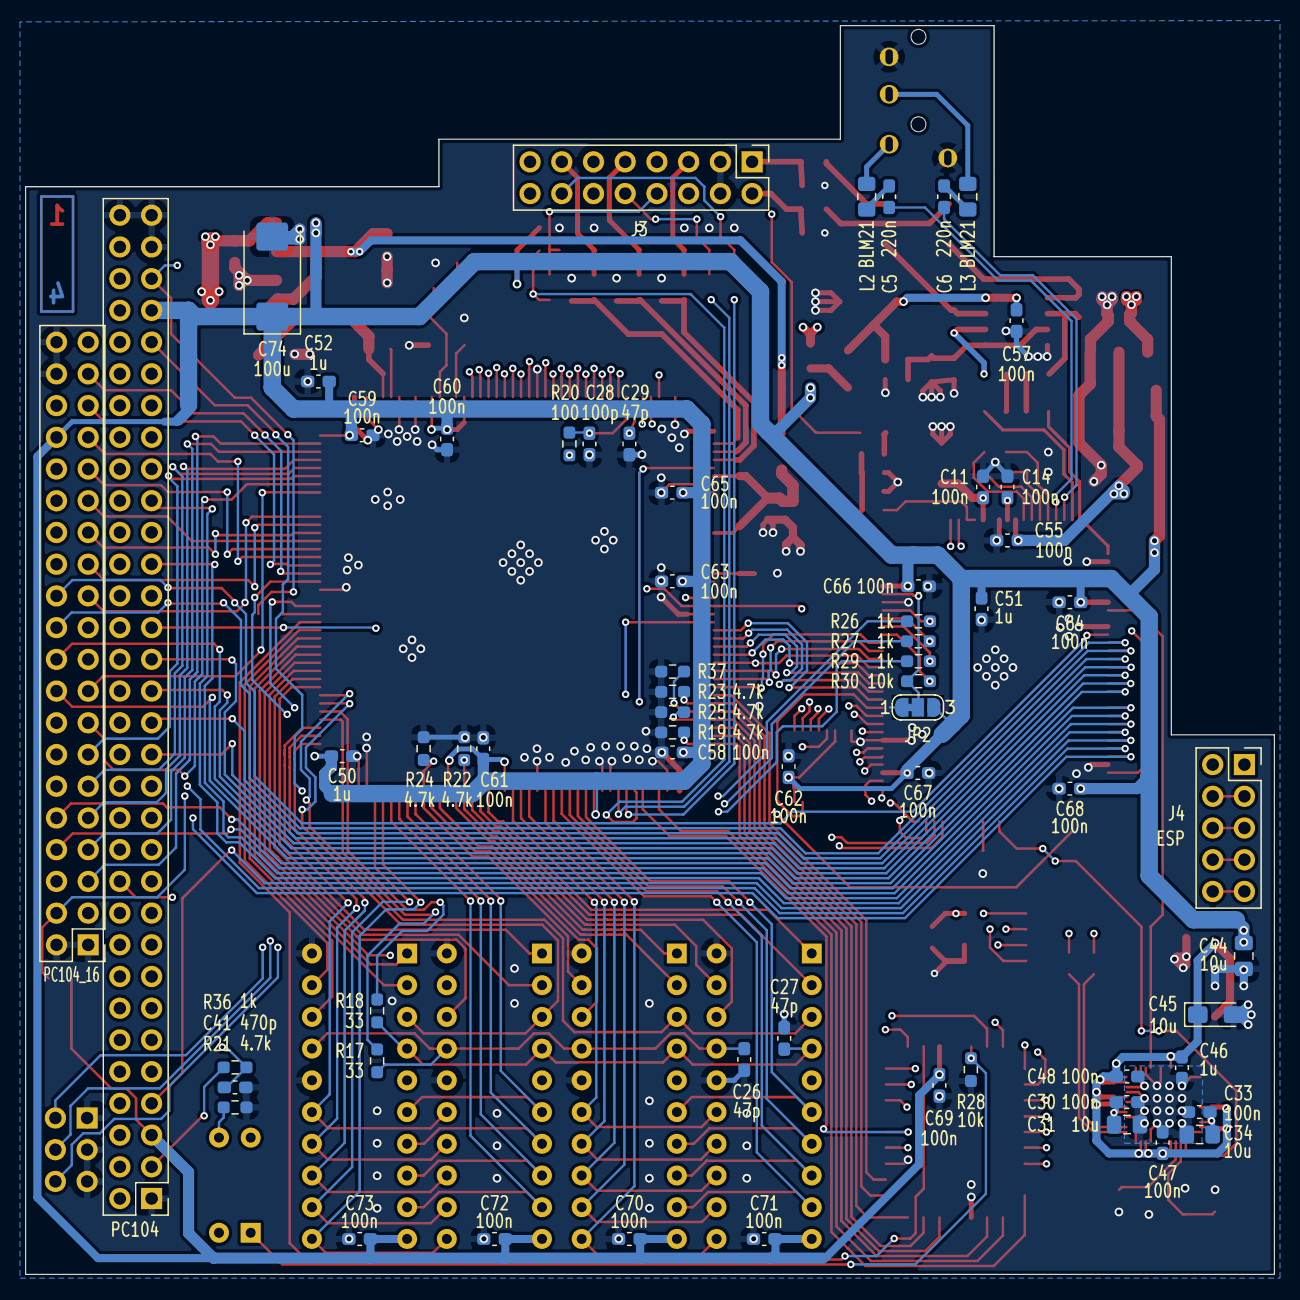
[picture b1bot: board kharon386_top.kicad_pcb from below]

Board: 4 copper layers, 100.0 x 100.0 mm, 153 parts (63 on the bottom side), 202 nets.
